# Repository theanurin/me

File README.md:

# Content Of My Landing Site

See [https://www.anurin.name](https://www.anurin.name)

## Development

```shell
docker run --interactive --rm --publish 127.0.0.1:4000:4000 --publish 127.0.0.1:4001:4001 --workdir "${PWD}" \
  --mount type=bind,source="${PWD}",target="${PWD}" --volume name-anurin-me-bundle-data:"${PWD}/vendor/bundle" \
  theanurin/jekyll:4.3.4-02
```

Browse to http://127.0.0.1:4000

## Setup Development Environment

Note: This repository uses Git Large File Storage (Git LFS) to store large binary files. See details in separate [document](./LFS.md)

```shell
git lfs install # required once per machine

git clone -b dev git@github.com:theanurin/me.git theanurin-me
cd theanurin-me

git config --local core.hooksPath .githooks
git submodule update --init
```

## References

- My Jekyll Theme - [jekyll-theme-anurina](https://github.com/theanurin/jekyll-theme-anurina)
- Base Jekyll Theme - https://github.com/Stavrospanakakis/jekyll-cv
- [https://github.com/pavlovalor](Pavló Valor)
- Wikipedia [Résumé](https://en.wikipedia.org/wiki/R%C3%A9sum%C3%A9)

https://roadmap.sh/backend
https://roadmap.sh/linux
https://roadmap.sh/devops

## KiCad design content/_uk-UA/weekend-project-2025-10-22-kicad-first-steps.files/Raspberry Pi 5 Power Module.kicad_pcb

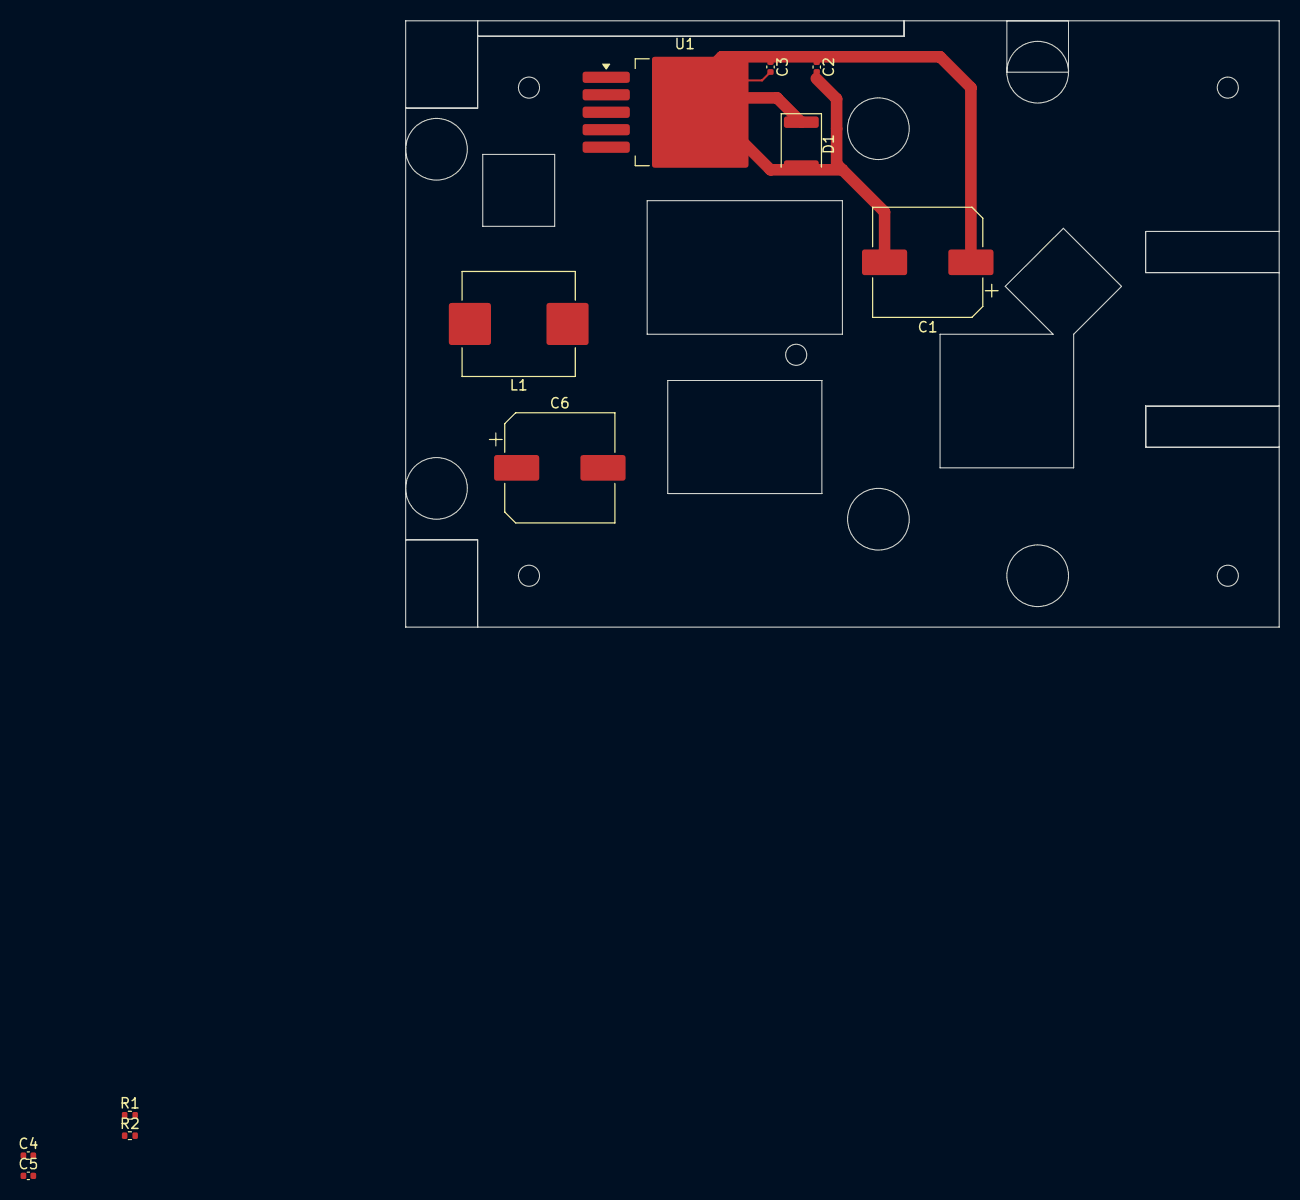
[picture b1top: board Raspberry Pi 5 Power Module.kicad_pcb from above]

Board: 2 copper layers, 85.0 x 59.0 mm, 11 parts (0 on the bottom side), 6 nets.

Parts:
C1: 220uF/50V; CP_Elec_10x10.5
C2, C3, C4: 1uF; C_0402_1005Metric
C5: 33nF; C_0402_1005Metric
C6: 220uF/10V; CP_Elec_10x10.5
D1: MBRD1045G; D_1812_4532Metric
L1: 47uH/5A; L_APV_APH1050
R1: 10K; R_0402_1005Metric
R2: 3.3K; R_0402_1005Metric
U1: XL4015E1; TO-263-5_TabPin3

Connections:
+5V(OUT): C4.1, C5.1, C6.1, L1.2, R1.1
+8~36V(IN): C1.1, C2.1, C3.1, U1.5 (VIN)
GND(IN): C1.2, C2.2, C4.2, C6.2, D1.2 (A), R2.2, U1.1 (GND)
unnamed: D1.1 (K), L1.1, U1.3 (SW)
unnamed: C5.2, R1.2, R2.1, U1.2 (FB)
unnamed: C3.2, U1.4 (VC)

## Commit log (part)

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2022-08-09 Work in progress
2025-04-25 Introduce layout_kinds
2025-04-25 Describe all companies
2025-04-25 Add CV Rigel layout
2025-05-12 add style for rigel layout
2025-10-28 Add LFS configuration
2025-10-28 Add parts of weekend-project-2025-10-18
2025-10-28 Add parts of weekend-project-2025-10-19
2025-10-28 Add parts of weekend-project-2025-10-22-kicad-first-steps
2025-11-06 Latest changes
2025-11-06 Remove submodule jekyll-theme-anurina. Move old content into obsolete-jekyll
2025-11-12 Add notes about Cubietruck's U-Boot installation
2025-11-12 Add few images for Lifepo4 battery based in MB31 elements
2025-12-17 Add few photos about Delta FR-48
2026-04-03 Add Mach3Version3.043.exe
2026-04-03 Add Delta's manuals
2026-04-03 Add few notes for SJCAM SJ4000 HD 1080P Review
2026-04-03 Add component: datasheets, images
2026-04-03 Add materials for connecting-a-generator-to-a-solar-inverter
2026-04-03 Init KiCAD project for Delta-FR48-REV04
2026-04-03 Add drilling by end-mill gcode
2026-04-03 Add school chairs project artifacts
2026-04-03 Some content moved to https://github.com/theanurin/gentoo-cubietruck
2026-04-03 CNC6040Z related content
2026-04-03 Add CAD of bathroom renovation
2026-04-03 Add oldest
2026-04-03 Add Leaf ZE0 notes
2026-04-03 Add interview-zelly-ai-2025-11.js
2026-04-03 Add few FreeCAD projects
2026-04-03 Add few images about Flatpack2 CAN control module
2026-04-21 In progress
2026-04-25 MVP in progress
2026-04-25 Fix CI workflow
2026-04-29 CV is almost human-ready
2026-04-29 Fix home URL
2026-04-29 Remove parts of obsolete stuff
2026-04-29 Checkout LFS files too
2026-04-29 Add CNAME
2026-04-29 CV review
2026-04-29 Configure IDE
2026-04-29 Finalizing MVP
2026-04-30 Migrate to 11ty. CV is included.
2026-05-01 Add one line to summary MVP for Open Graph (OG) tags
2026-05-01 Deploy update from v20260429 / 3f965a38d1c87c702a4383730d952220beea8fb2
2026-05-01 Deploy update from main / 6716ebe127a4695926bda35c8cf6e1b93f60baf3
2026-05-01 Fix OG links Add favicon
2026-05-01 Deploy update from main / 8679f93fc9d992352a14fdab41e04ce545ddf1bb
2026-05-01 Deploy update from v20260501-01 / 8679f93fc9d992352a14fdab41e04ce545ddf1bb
2026-05-01 Use base layout on the root(redirecting) page
2026-05-01 Deploy update from main / 2366c611fd8eff6d3747e9b8e72e397b90cdcd03
2026-05-01 Deploy update from v20260501-02 / 2366c611fd8eff6d3747e9b8e72e397b90cdcd03
2026-05-11 Update SITE_ANALYTICS_UNAMI_WEBSITE_ID
2026-05-11 Update data-website-id
2026-05-20 Add JSCut notes
2026-05-20 Add post weld machining gcode/svg
2026-05-20 Little fix of gcode
2026-05-22 Refactor milling path
2026-05-22 Rename GCode files
